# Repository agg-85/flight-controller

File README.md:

# STM32 Flight Controller Project
A custom STM32-based flight controller designed from the ground up for quadcopters. This project includes PCB design using KiCad and embedded firmware using Ardupilot.

## Features
- STM32 Microcontroller
- 6-axis IMU
- Barometer
- USB-C
- PWM
- I2C and SPI

## Hardware
| Component | Part |
|-----------|------|
| MCU | STM32F405, 168MHz, 1MB Flash |
| IMU | ICM-42688-P |
| Barometer | MS5611 |

## Status

- [ ] Hardware
  - [x] MCU Decoupling
  - [x] IMU Wiring
  - [x] Barometer Wiring
  - [X] USB-C Connection
  - [X] ESD Protection
  - [X] SWD Headers
  - [ ] Power management
  - [ ] ESC Pads
  - [ ] Complete schematic
  - [ ] PCB layout
  - [ ] Design review
  - [ ] Order PCB
  - [ ] Assemble board
        
- [ ] Firmware
  - [ ] Configure Ardupilot
  - [ ] Build Ardupilot
  - [ ] Flash firmware

- [ ] Testing
  - [ ] Mission Planner
  - [ ] Flight test

## Design Decisions

### STM32F405

The STM32F405 was selected because:
- Sufficient processing power for flight control
- Compatibility with ArduPilot
- Used in most commercial FCs, providing abundant documentation and examples

## Takeaways/Useful Facts

- SPI facilitates DMA, which offloads data transfers from the main MCU. This prevents processor lag. SPI needs pull up resistors for CS since it sets CS low to select devices. Use GPIO for CS instead of built-in NSS so that ArduPilot can handle CS lines through software.
-  IMU enhances GPS reliability in tunnels or areas with EM interference.
-  Each principal axis (pitch, roll, yaw) translates to accelerometer, gyroscope, and magnetometer.
-  Place smallest decoupling capacitors closest to pin to minimize trace inductance. Smaller capacitors filter high frequency noise, and inductive impedance is proportial to frequency.
-  Vref serves as a precise baseline voltage for ADCs and DACs, isolating noise and maintaining consistent voltage.
-  ESD protection for USB connector as TVS array, where TVS diodes acts as an open circuit when operating voltage is normal. When a voltage spike occurs, it acts as a short circuit to sink high current and clamps D+/D-.
-  NRST puts chip in known state (setting registers to default), used to activate bootloader when flashing new program (ex: through SWD interface)
-  SWD bypasses bootloader and can reset and flash MCU directly
-  BOOT0 needs pull-down resistor to avoid floating. DFU mode is entered when BOOT0 is high, and BOOT1 can be permanently tied to ground.
  
## Goals

The objective of this project is to design a flight controller from scratch while learning PCB design, embedded systems, and hardware debugging.

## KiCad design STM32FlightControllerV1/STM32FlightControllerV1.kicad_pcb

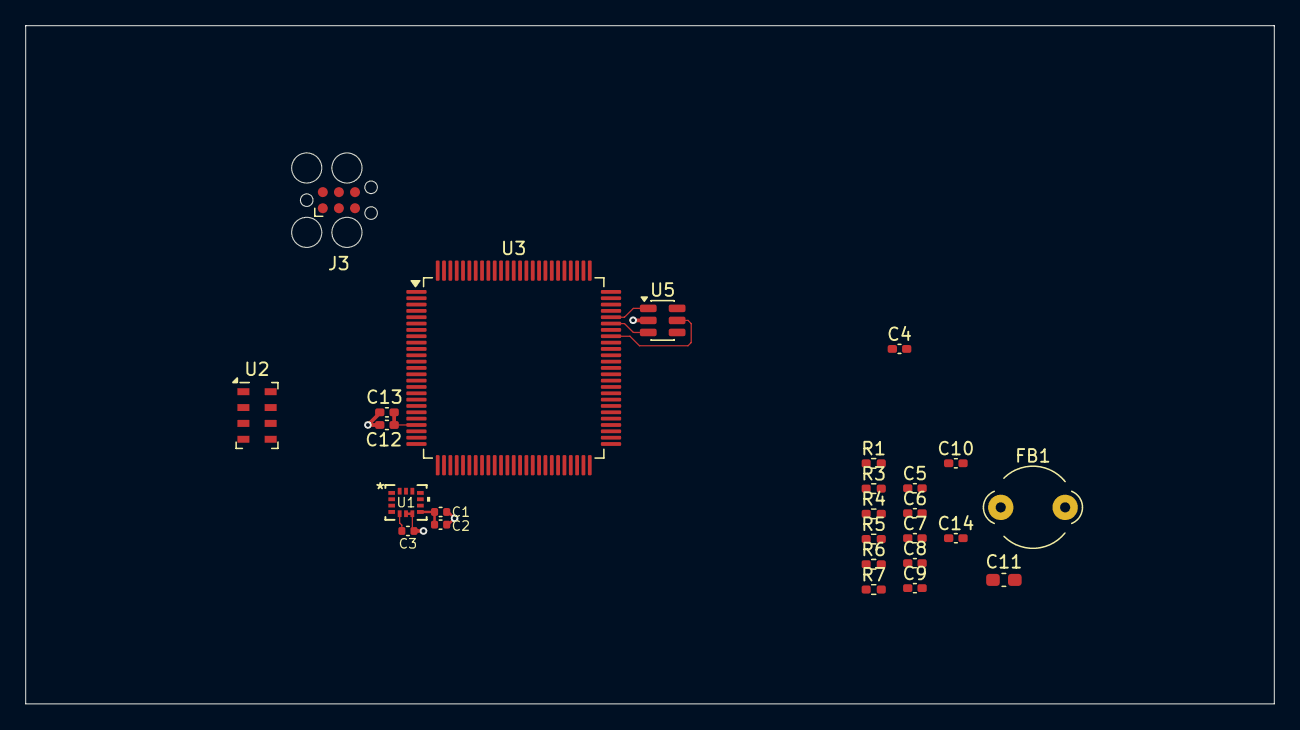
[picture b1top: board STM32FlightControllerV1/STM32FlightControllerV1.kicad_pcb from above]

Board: 2 copper layers, 98.5 x 53.5 mm, 26 parts (0 on the bottom side), 15 nets.

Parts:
C1: 0.1u; C_0402_1005Metric
C2: 2.2u; C_0402_1005Metric
C3: 10n; C_0402_1005Metric
C4, C5, C6, C7, C8, C9, C10, C13: 100n; C_0402_1005Metric_Pad0.74x0.62mm_HandSolder
C11: 10u; C_0603_1608Metric_Pad1.08x0.95mm_HandSolder
C12: 1u; C_0402_1005Metric_Pad0.74x0.62mm_HandSolder
C14: 0.1u; C_0402_1005Metric_Pad0.74x0.62mm_HandSolder
FB1: FerriteBead; LairdTech_28C0236-0JW-10
J3: Conn_ARM_SWD_TagConnect_TC2030; Tag-Connect_TC2030-IDC-FP_2x03_P1.27mm_Vertical
R1, R6, R7: 10k; R_0402_1005Metric_Pad0.72x0.64mm_HandSolder
R3, R4: 5.1k; R_0402_1005Metric_Pad0.72x0.64mm_HandSolder
R5: 47; R_0402_1005Metric_Pad0.72x0.64mm_HandSolder
U1: ICM-42688-P; LGA14_2P5X3X0P91_TDK
U2: MS5611-01BA; LGA-8_3x5mm_P1.25mm
U3: STM32F405VGTx; LQFP-100_14x14mm_P0.5mm
U5: USBLC6-2SC6; SOT-23-6

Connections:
3V3_FC: C1.2, C2.2, C3.1, C4.2, C5.1, C6.1, C7.1, C8.1, C9.1, C10.1, C11.1, FB1.1, R1.1, U1.5 (VDDIO), U1.8 (VDD), U2.1 (VDD), U3.11 (VDD), U3.19 (VDD), U3.28 (VDD), U3.50 (VDD), U3.75 (VDD), U3.100 (VDD)
BARO_CS: R1.2, U2.4 (CSB), U2.5 (CSB)
BOOT0: R6.1, U3.94 (BOOT0)
BOOT1: R7.2, U3.37 (PB2)
GND: C1.1, C2.1, C3.2, C4.1, C5.2, C6.2, C7.2, C8.2, C9.2, C10.2, C11.2, C12.2, C13.2, C14.2, R3.2, R4.2, R6.2, U1.6 (GND), U1.7 (RESV), U2.2 (PS), U2.3 (GND), U3.20 (VSSA), U5.2 (GND)
NRST: C14.1, U3.14 (NRST)
unnamed: U3.10 (VSS), U3.27 (VSS), U3.74 (VSS), U3.99 (VSS)
SPI1_MISO: U1.1 (AP_SDO/AP_AD0), U2.8 (SCLK)
SPI1_MOSI: U1.12 (AP_CS), U2.7 (SDI/SDA)
SPI1_SCK: U1.13 (AP_SCL/AP_SCLK), U2.6 (SDO)
USB_DM: U3.70 (PA11), U5.3 (I/O2), U5.4 (I/O2)
USB_DP: U3.71 (PA12), U5.1 (I/O1), U5.6 (I/O1)
USB_VBUS: U3.68 (PA9), U5.5 (VBUS)
VDDA: C12.1, C13.1, FB1.2, R5.2, U3.22 (VDDA)
VREF+: R5.1, U3.21 (VREF+)

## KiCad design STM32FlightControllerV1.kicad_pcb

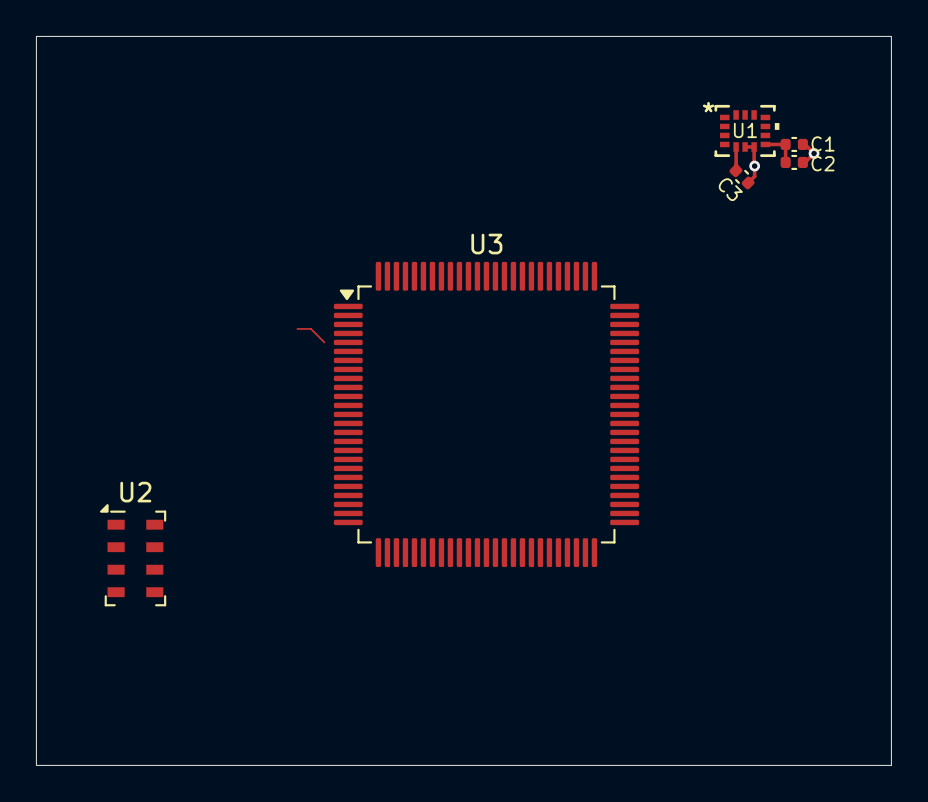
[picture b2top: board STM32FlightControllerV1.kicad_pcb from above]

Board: 2 copper layers, 47.5 x 40.5 mm, 6 parts (0 on the bottom side), 4 nets.

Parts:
C1: 0.1u; C_0402_1005Metric
C2: 2.2u; C_0402_1005Metric
C3: 10n; C_0402_1005Metric
U1: ICM-42688-P; LGA14_2P5X3X0P91_TDK
U2: MS5611-01BA; LGA-8_3x5mm_P1.25mm
U3: STM32F405VGTx; LQFP-100_14x14mm_P0.5mm

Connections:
+1V8: C1.2, C2.2, C3.1, U1.7 (RESV), U1.8 (VDD)
GND: C1.1, C2.1, C3.2, U2.2 (PS), U2.3 (GND)
unnamed: U2.4 (CSB), U2.5 (CSB)
unnamed: U3.10 (VSS), U3.27 (VSS), U3.74 (VSS), U3.99 (VSS)
